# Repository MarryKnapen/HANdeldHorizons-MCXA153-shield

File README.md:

# FRDM-MCXA153 Arduino + MirkoBUS shield KICAD template

- Can be converted to Arduino Only or MikroBUS only template

# DO NOT USE THIS TEMPLATE, NO GUARANTEE IS GIVEN. THIS PRODUCT IS INCOMPLETE AND STILL REQUIRES PHYSICAL VERIFICATION OF COMPATIBILITY

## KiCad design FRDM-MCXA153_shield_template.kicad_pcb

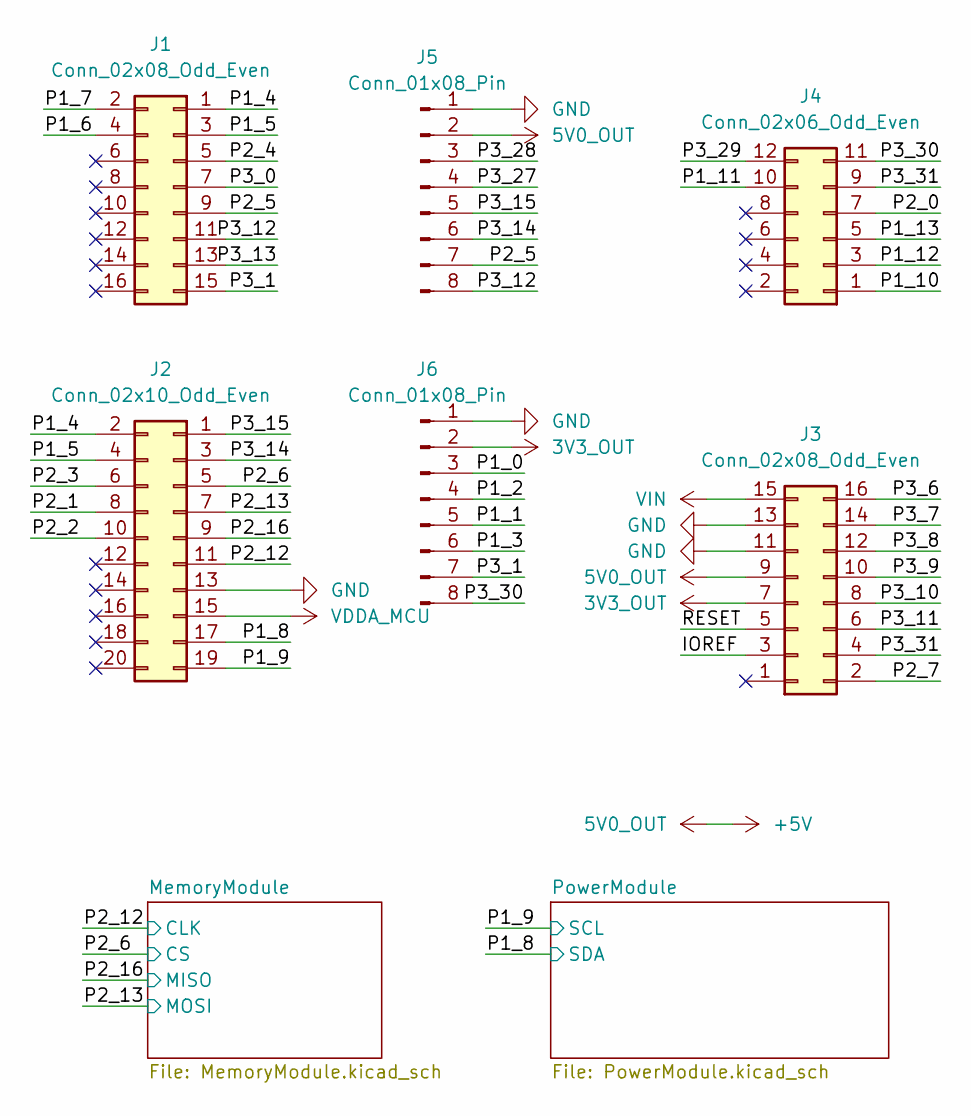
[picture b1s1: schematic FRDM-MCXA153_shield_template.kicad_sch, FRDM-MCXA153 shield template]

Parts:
J1, J3: Conn_02x08_Odd_Even; PinHeader_2x08_P2.54mm_Vertical
J2: Conn_02x10_Odd_Even; PinHeader_2x10_P2.54mm_Vertical
J4: Conn_02x06_Odd_Even; PinHeader_2x06_P2.54mm_Vertical
J5, J6: Conn_01x08_Pin; PinHeader_1x08_P2.54mm_Vertical

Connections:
3V3_OUT: J3.7, J6.2
+5V: J3.9, J5.2; also elsewhere on the board
/IOREF: J3.3
/P1_0: J6.3
/P1_1: J6.5
/P1_2: J6.4
/P1_3: J6.6
/P1_4: J1.1, J2.2
/P1_5: J1.3, J2.4
/P1_6: J1.4
/P1_7: J1.2
/P1_8: J2.17; also elsewhere on the board
/P1_9: J2.19; also elsewhere on the board
/P1_10: J4.1
/P1_11: J4.10
/P1_12: J4.3
/P1_13: J4.5
/P2_0: J4.7
/P2_1: J2.8
/P2_2: J2.10
/P2_3: J2.6
/P2_4: J1.5
/P2_5: J1.9, J5.7
/P2_6: J2.5; also elsewhere on the board
/P2_7: J3.2
/P2_12: J2.11; also elsewhere on the board
/P2_13: J2.7; also elsewhere on the board
/P2_16: J2.9; also elsewhere on the board
/P3_0: J1.7
/P3_1: J1.15, J6.7
/P3_6: J3.16
/P3_7: J3.14
/P3_8: J3.12
/P3_9: J3.10
/P3_10: J3.8
/P3_11: J3.6
/P3_12: J1.11, J5.8
/P3_13: J1.13
/P3_14: J2.3, J5.6
/P3_15: J2.1, J5.5
/P3_27: J5.4
/P3_28: J5.3
/P3_29: J4.12
/P3_30: J4.11, J6.8
/P3_31: J3.4, J4.9
/RESET: J3.5
GND: J2.13, J3.11, J3.13, J5.1, J6.1; also elsewhere on the board
VDDA_MCU: J2.15
VIN: J3.15

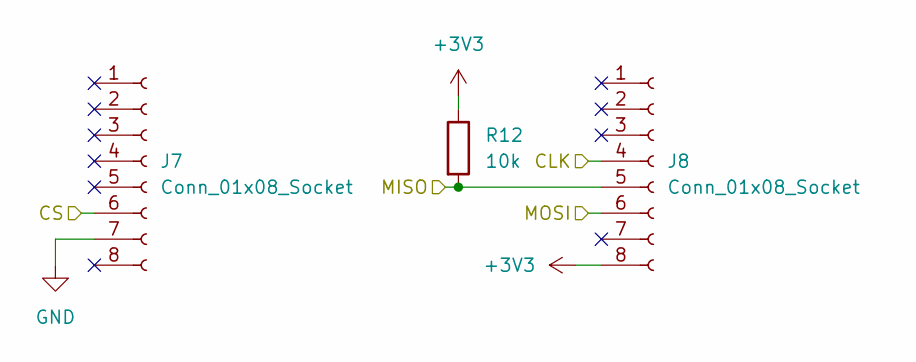
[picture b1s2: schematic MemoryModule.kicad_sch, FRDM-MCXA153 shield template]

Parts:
J7, J8: Conn_01x08_Socket; PinSocket_1x08_P2.54mm_Vertical
R12: 10k; R_1206_3216Metric_Pad1.30x1.75mm_HandSolder

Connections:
+3V3: J8.8, R12.1
/P2_6: J7.6; also elsewhere on the board
/P2_12: J8.4; also elsewhere on the board
/P2_13: J8.6; also elsewhere on the board
/P2_16: J8.5, R12.2; also elsewhere on the board
GND: J7.7; also elsewhere on the board

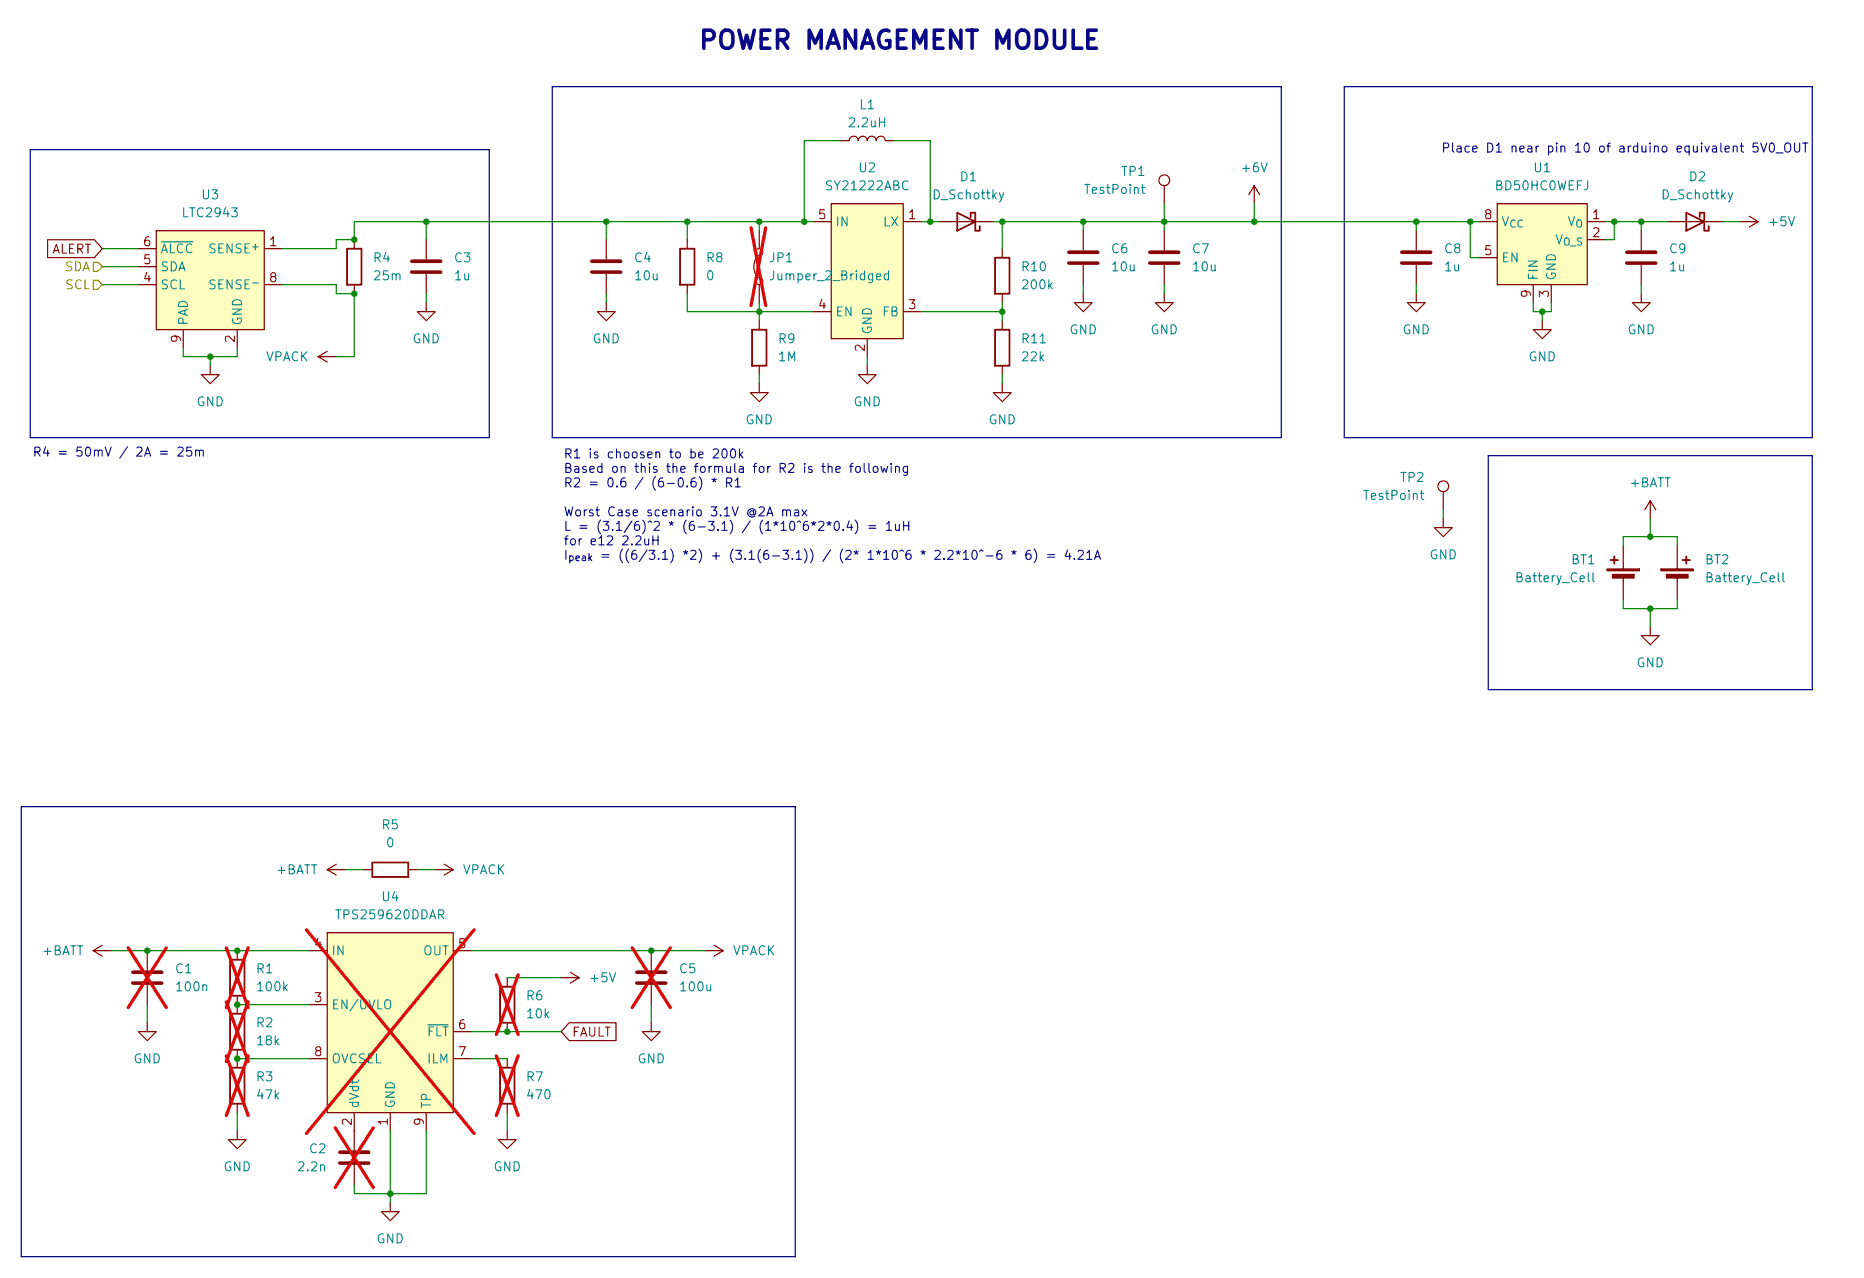
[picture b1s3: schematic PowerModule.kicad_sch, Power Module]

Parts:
BT1, BT2: Battery_Cell; SolderWire-0.75sqmm_1x02_P4.8mm_D1.25mm_OD2.3mm
C1: 100n; C_1206_3216Metric_Pad1.33x1.80mm_HandSolder; not fitted
C2: 2.2n; C_1206_3216Metric_Pad1.33x1.80mm_HandSolder; not fitted
C3, C8, C9: 1u; C_1206_3216Metric_Pad1.33x1.80mm_HandSolder
C4, C6, C7: 10u; C_1206_3216Metric_Pad1.33x1.80mm_HandSolder
C5: 100u; C_1206_3216Metric_Pad1.33x1.80mm_HandSolder; not fitted
D1: D_Schottky; D_PowerDI-123
D2: D_Schottky; D_MicroSMP_AK
JP1: Jumper_2_Bridged; PinHeader_1x02_P2.54mm_Vertical; not fitted
L1: 2.2uH; IND_LQH5BPN_MUR
R1: 100k; R_1206_3216Metric_Pad1.30x1.75mm_HandSolder; not fitted
R2: 18k; R_1206_3216Metric_Pad1.30x1.75mm_HandSolder; not fitted
R3: 47k; R_1206_3216Metric_Pad1.30x1.75mm_HandSolder; not fitted
R4: 25m; R_1206_3216Metric_Pad1.30x1.75mm_HandSolder
R5, R8: 0; R_1206_3216Metric_Pad1.30x1.75mm_HandSolder
R6: 10k; R_1206_3216Metric_Pad1.30x1.75mm_HandSolder; not fitted
R7: 470; R_1206_3216Metric_Pad1.30x1.75mm_HandSolder; not fitted
R9: 1M; R_1206_3216Metric_Pad1.30x1.75mm_HandSolder
R10: 200k; R_1206_3216Metric_Pad1.30x1.75mm_HandSolder
R11: 22k; R_1206_3216Metric_Pad1.30x1.75mm_HandSolder
TP1, TP2: TestPoint; PinHeader_1x01_P2.54mm_Vertical
U1: BD50HC0WEFJ; HTSOP-J8
U2: SY21222ABC; SOT-23-6
U3: LTC2943; DFN-8-1EP_3x3mm_P0.5mm_EP1.66x2.38mm
U4: TPS259620DDAR; SOIC-8-1EP_3.9x5.75mm_P1.27mm_EP2.4x3.1mm; not fitted

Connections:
+5V: D2.1 (K), R6.1; also elsewhere on the board
+6V: C6.1, C7.1, C8.1, D1.1 (K), R10.1, TP1.1, U1.5 (EN), U1.8 (V_{CC})
+BATT: BT1.1 (+), BT2.1 (+), C1.1, R1.1, R5.1, U4.4 (IN)
/P1_8: U3.5 (SDA); also elsewhere on the board
/P1_9: U3.4 (SCL); also elsewhere on the board
ALERT: U3.6 (~ALCC)
FAULT: R6.2, U4.6 (~FLT)
GND: BT1.2 (-), BT2.2 (-), C1.2, C2.2, C3.2, C4.2, C5.2, C6.2, C7.2, C8.2, C9.2, R3.2, R7.2, R9.2, R11.2, TP2.1, U1.3 (GND), U1.9 (FIN), U2.2 (GND), U3.2 (GND), U3.3 (GND), U3.7 (GND), U3.9 (PAD), U4.1 (GND), U4.9 (TP); also elsewhere on the board
unnamed: D1.2 (A), L1.2, U2.1 (LX)
unnamed: C9.1, D2.2 (A), U1.1 (V_{O}), U1.2 (V_{O_S})
unnamed: JP1.1 (A), R8.2, R9.1, U2.4 (EN)
unnamed: C3.1, C4.1, JP1.2 (B), L1.1, R4.1, R8.1, U2.5 (IN), U3.1 (SENSE^{+})
unnamed: R10.2, R11.1, U2.3 (FB)
unnamed: R1.2, R2.1, U4.3 (EN/UVLO)
unnamed: R7.1, U4.7 (ILM)
unnamed: R2.2, R3.1, U4.8 (OVCSEL)
unnamed: C2.1, U4.2 (dVdt)
VPACK: C5.1, R4.2, R5.2, U3.8 (SENSE^{-}), U4.5 (OUT)

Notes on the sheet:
R4 = 50mV / 2A = 25m
Place D1 near pin 10 of arduino equivalent 5V0_OUT
POWER MANAGEMENT MODULE
R1 is choosen to be 200k Based on this the formula for R2 is the following R2 = 0.6 / (6-0.6) * R1 Worst Case scenario 3.1V @2A max L = (3.1/6)^2 * (6-3.1) / (1*10^6*2*0.4) = 1uH for e12 2.2uH I_{peak} = ((6/3.1) *2) + (3.1(6-3.1)) / (2* 1*10^6 * 2.2*10^-6 * 6) = 4.21A

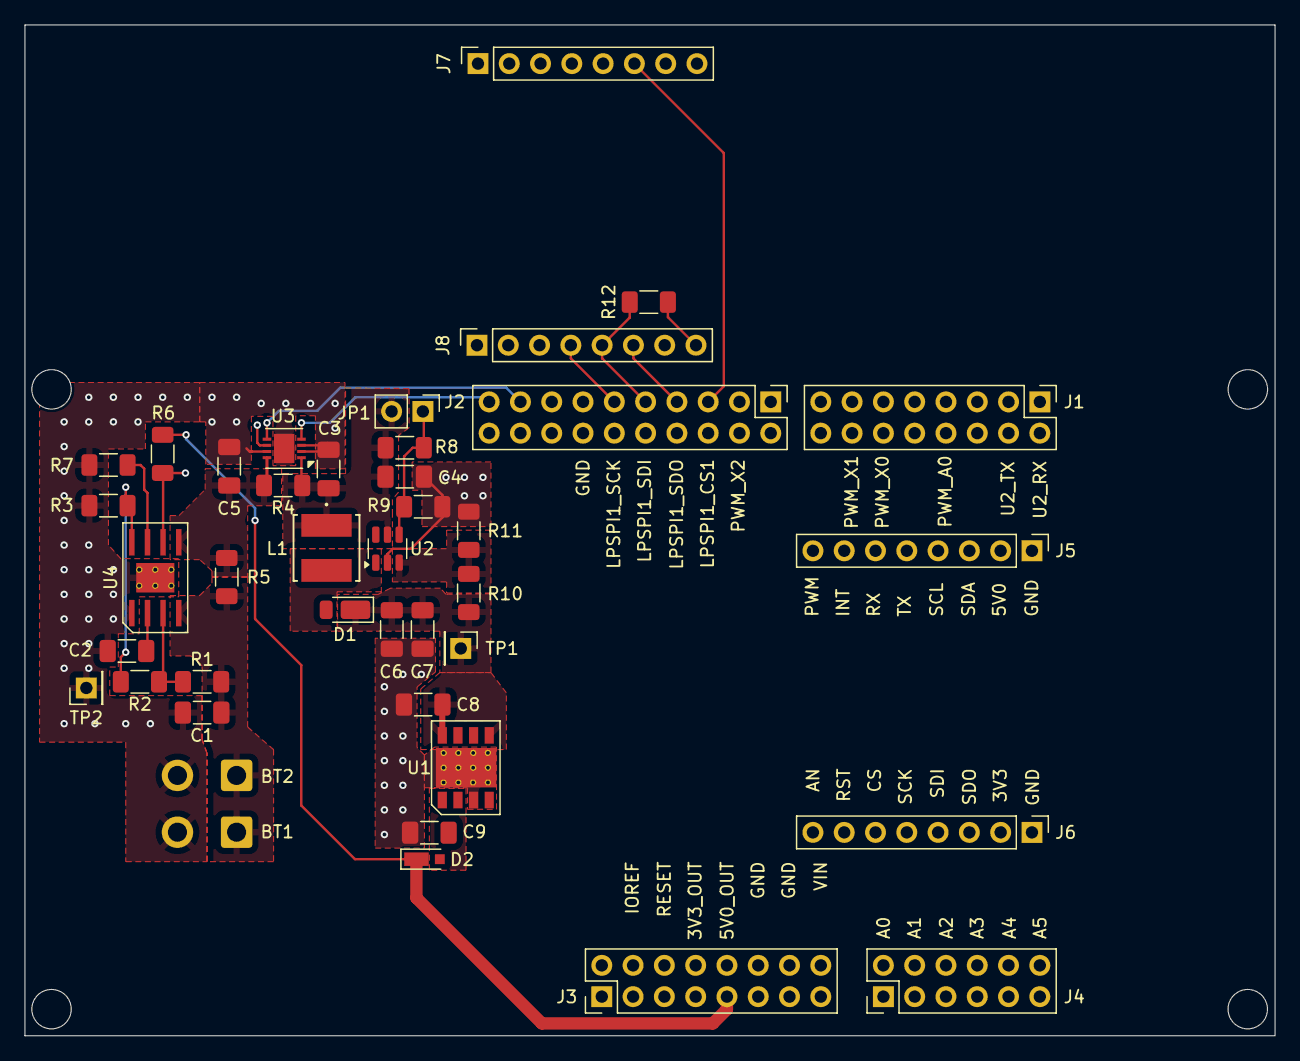
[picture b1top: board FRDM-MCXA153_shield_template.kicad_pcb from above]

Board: 2 copper layers, 101.5 x 82.1 mm, 45 parts (0 on the bottom side), 32 nets.

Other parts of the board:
H1, H2, H3, H4: MountingHole; MountingHole_3.2mm_M3_ISO7380

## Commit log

2025-05-06 add power module
2025-05-06 add memory module and increase size of shield
